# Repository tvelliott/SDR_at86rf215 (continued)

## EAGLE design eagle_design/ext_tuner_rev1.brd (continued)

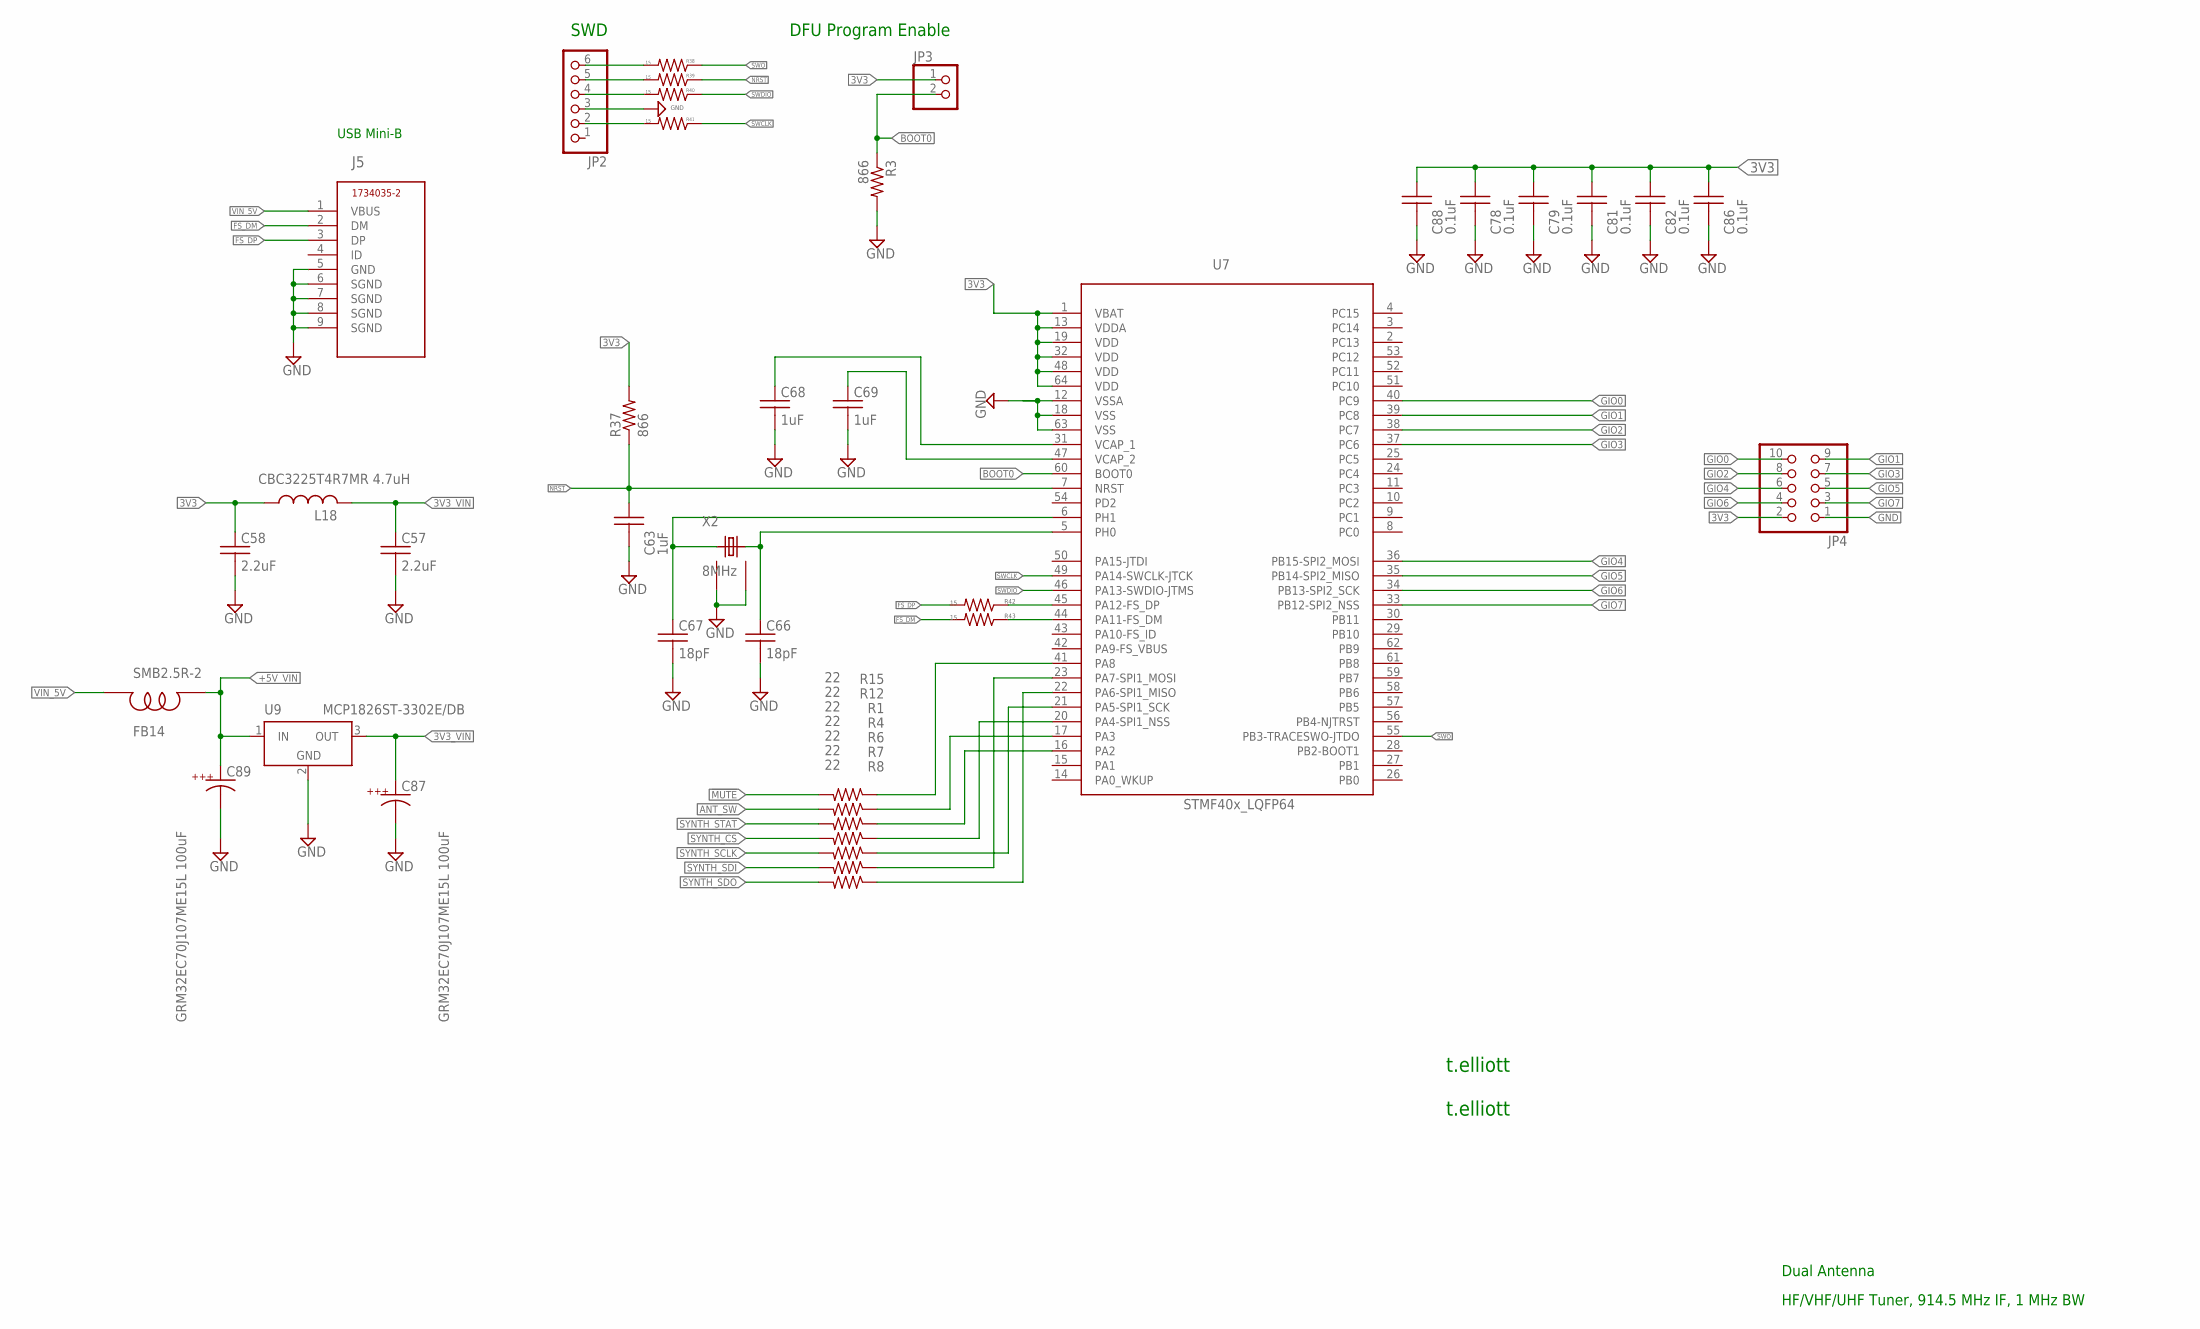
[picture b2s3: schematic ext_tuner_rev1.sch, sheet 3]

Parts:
C57, C58: 2.2uF; C0603
C63, C68, C69: 1uF; C0402@1
C66, C67: 18pF; C0402@1
C78, C79, C81, C82, C86, C88: 0.1uF; C0402@1
C87, C89: GRM32EC70J107ME15L 100uF; 1210K
FB14: SMB2.5R-2; SMB2.5-2
J5: 1734035-2
JP2: PINHD-1X6; 1X06
JP3: PINHD-1X2; 1X02
JP4: PINHD-2X5; 2X05
L18: CBC3225T4R7MR 4.7uH; L3225M; PARTNUMBER ELJ-PA331KF
R1, R4, R6, R7, R8, R12, R15: 22; R0603_COMPACT
R3: 866; R0603
R37: 866; 0603
R38, R39, R40, R41, R42, R43: 15; 0402$1
U7: STM32_STM32F40X_LQFP64RGT6; STM32_LQFP64
U9: MCP1826ST-3302E/DB; SOT223
X2: 8MHz; ECS_CRYSTAL_ECS-250-20-30B-DU_CRYSTAL

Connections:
3V3: C58.1, C78.1, C79.1, C81.1, C82.1, C86.1, C88.1, JP3.1, JP4.2, L18.1, R37.2, U7.1 (VBAT), U7.13 (VDDA), U7.19 (VDD), U7.32 (VDD), U7.48 (VDD), U7.64 (VDD); also elsewhere on the board
3V3_VIN: C57.1, C87.A, L18.2, U9.3 (OUT)
!MUTE: R15.2; also elsewhere on the board
+5V_VIN: C89.A, FB14.P$1, U9.1 (IN); also elsewhere on the board
ANT_SW: R12.2; also elsewhere on the board
BOOT0: JP3.2, R3.1, U7.60 (BOOT0)
FS_DM: J5.2 (DM), R43.2
FS_DP: J5.3 (DP), R42.2
GIO0: JP4.10, U7.40 (PC9)
GIO1: JP4.9, U7.39 (PC8)
GIO2: JP4.8, U7.38 (PC7)
GIO3: JP4.7, U7.37 (PC6)
GIO4: JP4.6, U7.36 (PB15-SPI2_MOSI)
GIO5: JP4.5, U7.35 (PB14-SPI2_MISO)
GIO6: JP4.4, U7.34 (PB13-SPI2_SCK)
GIO7: JP4.3, U7.33 (PB12-SPI2_NSS)
GND: C57.2, C58.2, C63.2, C66.2, C67.2, C68.2, C69.2, C78.2, C79.2, C81.2, C82.2, C86.2, C87.C, C88.2, C89.C, J5.5 (GND), J5.6 (SGND), J5.7 (SGND), J5.8 (SGND), J5.9 (SGND), JP2.3, JP4.1, R3.2, U7.12 (VSSA), U7.18 (VSS), U7.63 (VSS), U9.2 (GND), U9.4 (GND), X2.GND@1 (GND), X2.GND@2 (GND); also elsewhere on the board
unnamed: R6.1, U7.21 (PA5-SPI1_SCK)
unnamed: R8.1, U7.22 (PA6-SPI1_MISO)
unnamed: R7.1, U7.23 (PA7-SPI1_MOSI)
unnamed: R4.1, U7.20 (PA4-SPI1_NSS)
unnamed: C67.1, U7.6 (PH1), X2.1
unnamed: C66.1, U7.5 (PH0), X2.3
unnamed: R42.1, U7.45 (PA12-FS_DP)
unnamed: R43.1, U7.44 (PA11-FS_DM)
unnamed: C69.1, U7.47 (VCAP_2)
unnamed: C68.1, U7.31 (VCAP_1)
unnamed: JP2.6, R38.2
unnamed: JP2.5, R39.2
unnamed: JP2.4, R40.2
unnamed: JP2.2, R41.2
unnamed: R1.1, U7.16 (PA2)
unnamed: R12.1, U7.17 (PA3)
unnamed: R15.1, U7.41 (PA8)
NRST: C63.1, R37.1, R39.1, U7.7 (NRST)
SWCLK: R41.1, U7.49 (PA14-SWCLK-JTCK)
SWDIO: R40.1, U7.46 (PA13-SWDIO-JTMS)
SWO: R38.1, U7.55 (PB3-TRACESWO-JTDO)
SYNTH_CS: R4.2; also elsewhere on the board
SYNTH_SCLK: R6.2; also elsewhere on the board
SYNTH_SDI: R7.2; also elsewhere on the board
SYNTH_SDO: R8.2; also elsewhere on the board
SYNTH_STAT: R1.2; also elsewhere on the board
VIN_5V: FB14.P$2, J5.1 (VBUS)

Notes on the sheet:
SWD
USB Mini-B
t.elliott
Dual Antenna
DFU Program Enable
HF/VHF/UHF Tuner, 914.5 MHz IF, 1 MHz BW

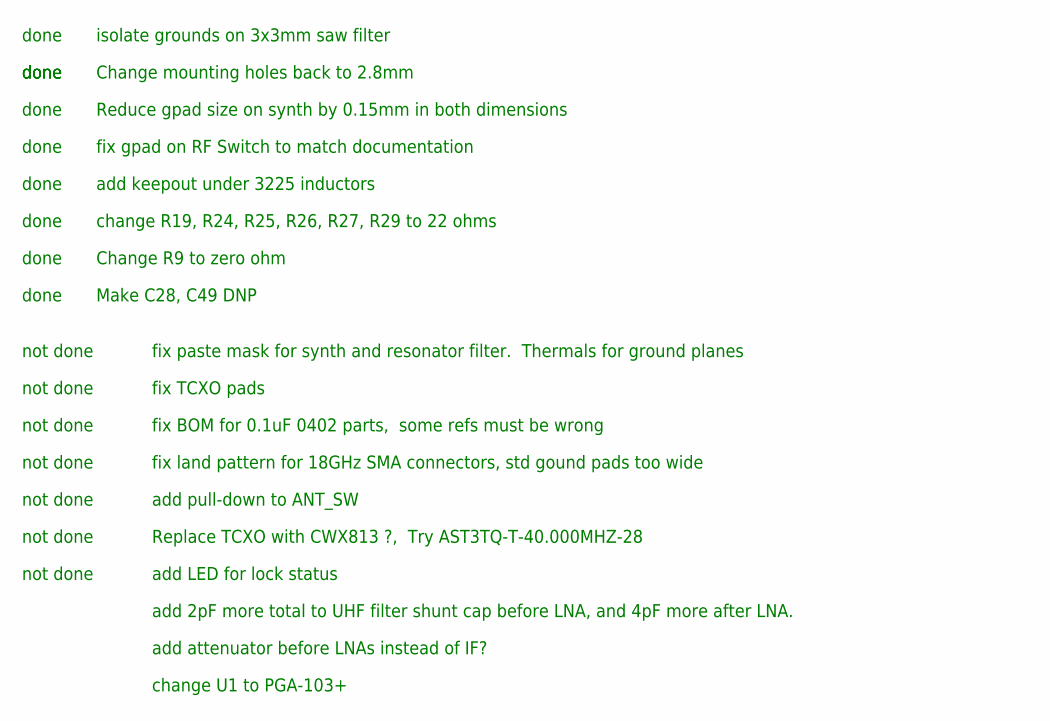
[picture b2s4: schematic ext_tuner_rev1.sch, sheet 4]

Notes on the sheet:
Change mounting holes back to 2.8mm
Reduce gpad size on synth by 0.15mm in both dimensions
fix gpad on RF Switch to match documentation
done
not done
fix paste mask for synth and resonator filter. Thermals for ground planes
fix TCXO pads
add keepout under 3225 inductors
fix BOM for 0.1uF 0402 parts, some refs must be wrong
fix land pattern for 18GHz SMA connectors, std gound pads too wide
add pull-down to ANT_SW
change R19, R24, R25, R26, R27, R29 to 22 ohms
Replace TCXO with CWX813 ?, Try AST3TQ-T-40.000MHZ-28
add LED for lock status
Change R9 to zero ohm
Make C28, C49 DNP
isolate grounds on 3x3mm saw filter
add 2pF more total to UHF filter shunt cap before LNA, and 4pF more after LNA.
add attenuator before LNAs instead of IF?
change U1 to PGA-103+

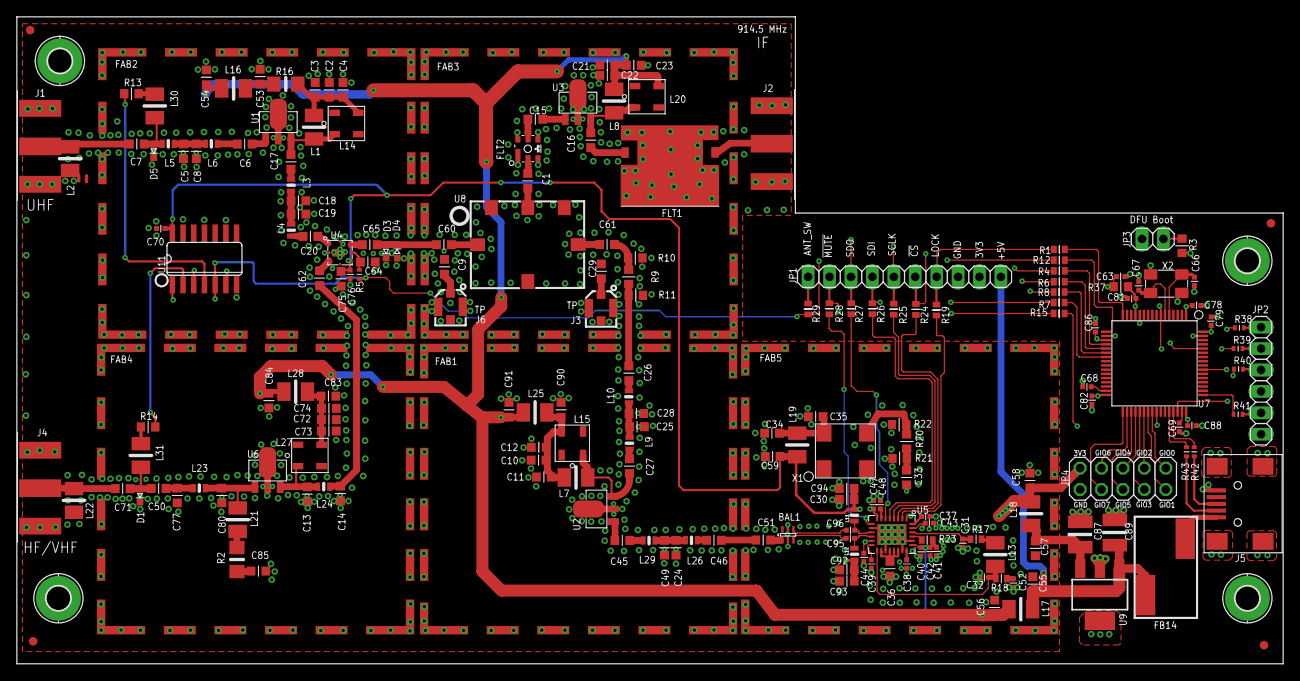
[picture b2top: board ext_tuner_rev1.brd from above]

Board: 4 copper layers, 150.2 x 76.7 mm, 206 parts (0 on the bottom side), 124 nets.

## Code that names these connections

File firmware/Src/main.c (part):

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        * Output
        * EVENT_OUT
        * EXTI
     PA8   ------> USB_OTG_FS_SOF
     PA11   ------> USB_OTG_FS_DM
     PA12   ------> USB_OTG_FS_DP
*/
static void MX_GPIO_Init( void )
{
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

  //display pins, all output
  //PG0 = DISP_RS
  //PG1 = DISP_SI
  //PG2 = DISP_CSB
  //PG3 = DISP_SCL
  //PG4 = DISP_RST
  GPIO_InitStruct.Pin = GPIO_PIN_0 | GPIO_PIN_1 | GPIO_PIN_2 | GPIO_PIN_3 | GPIO_PIN_4;
  GPIO_InitStruct.Mode = GPIO_MODE_OUTPUT_PP;
  GPIO_InitStruct.Pull = GPIO_NOPULL;
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

  //MCO2 output
  /*Configure GPIO pin : PC9 */
  GPIO_InitStruct.Pin = GPIO_PIN_9;
  GPIO_InitStruct.Mode = GPIO_MODE_AF_PP;
  GPIO_InitStruct.Pull = GPIO_NOPULL;
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
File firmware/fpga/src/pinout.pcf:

set_io AT_MISO B1
set_io AT_MOSI C1
set_io AT_SCLK D1
set_io AT_IRQ D2
set_io AT_CS C2
set_io AT_RESET_N R3
set_io FPGA_RXCLK J3
set_io FPGA_RX24 F1
set_io FPGA_TXCLK T3
set_io FPGA_TX_24_900 T2
set_io FPGA_RX900 T1
set_io LED2 A1 
set_io LED3 A2 
set_io clk_in R9 
set_io AUDIO_SDIN T8 
set_io AUDIO_SCLK T7 
set_io AUDIO_LRCLK T6 
set_io AUDIO_MCLK T5 
set_io CBSEL P13
set_io TUNER_SCK B10
set_io TUNER_MOSI B9
set_io TUNER_CS B8
set_io TUNER_MISO A9
set_io BT1 A5
set_io BT2 A6
set_io BT3 A7
set_io BT4 B5 
set_io BT5 B6 
set_io BT6 B7 
set_io A0 C16 
set_io A1 T15 
set_io A2 R16 
set_io A3 R15 
set_io A4 P16 
set_io A5 P15 
set_io A6 N16 
set_io A7 M16 
set_io A8 M15 
set_io A9 L16 
set_io A10 T14 
set_io A11 R14  
set_io A12 P14 
set_io A13 L14 
set_io A14 D14 
set_io A15 C14 
set_io D0 D16 
set_io D1 D15 
set_io D2 B16 
set_io D3 B15 
set_io D4 A16 
set_io D5 A15 
set_io D6 E16 
set_io D7 F15 
set_io D8 F16 
set_io D9 G15 
set_io D10 G16 
set_io D11 J15 
set_io D12 J16 
set_io D13 K15 
set_io D14 K16 
set_io D15 T16 
set_io FSMC_NOE F14 
set_io FSMC_NWE H14 
set_io FSMC_NE1 J14 
set_io FSMC_NE4 K14 
set_io FSMC_NL_NADV B14
set_io FPGA_SPI_SCLK R10
set_io FPGA_SPI_MOSI P10
set_io FPGA_SPI_MISO N12
set_io FPGA_SPI_CS R12 
set_io FSMC_CLK_IN K9 
set_io MIC_CLK R6 
set_io MIC_DATA R5 

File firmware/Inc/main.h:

//MIT License
//
//Copyright (c) 2018 tvelliott
//
//Permission is hereby granted, free of charge, to any person obtaining a copy
//of this software and associated documentation files (the "Software"), to deal
//in the Software without restriction, including without limitation the rights
//to use, copy, modify, merge, publish, distribute, sublicense, and/or sell
//copies of the Software, and to permit persons to whom the Software is
//furnished to do so, subject to the following conditions:
//
//The above copyright notice and this permission notice shall be included in all
//copies or substantial portions of the Software.
//
//THE SOFTWARE IS PROVIDED "AS IS", WITHOUT WARRANTY OF ANY KIND, EXPRESS OR
//IMPLIED, INCLUDING BUT NOT LIMITED TO THE WARRANTIES OF MERCHANTABILITY,
//FITNESS FOR A PARTICULAR PURPOSE AND NONINFRINGEMENT. IN NO EVENT SHALL THE
//AUTHORS OR COPYRIGHT HOLDERS BE LIABLE FOR ANY CLAIM, DAMAGES OR OTHER
//LIABILITY, WHETHER IN AN ACTION OF CONTRACT, TORT OR OTHERWISE, ARISING FROM,
//OUT OF OR IN CONNECTION WITH THE SOFTWARE OR THE USE OR OTHER DEALINGS IN THE
//SOFTWARE.



/* Define to prevent recursive inclusion -------------------------------------*/
#ifndef __MAIN_H__
#define __MAIN_H__

/* Includes ------------------------------------------------------------------*/

/* USER CODE BEGIN Includes */

/* USER CODE END Includes */

/* Private define ------------------------------------------------------------*/

#define MCO_Pin GPIO_PIN_9
#define MCO_GPIO_Port GPIOC
#define RMII_MDC_Pin GPIO_PIN_1
#define RMII_MDC_GPIO_Port GPIOC
#define RMII_REF_CLK_Pin GPIO_PIN_1
#define RMII_REF_CLK_GPIO_Port GPIOA
#define RMII_MDIO_Pin GPIO_PIN_2
#define RMII_MDIO_GPIO_Port GPIOA
#define RMII_CRS_DV_Pin GPIO_PIN_7
#define RMII_CRS_DV_GPIO_Port GPIOA
#define RMII_RXD0_Pin GPIO_PIN_4
#define RMII_RXD0_GPIO_Port GPIOC
#define RMII_RXD1_Pin GPIO_PIN_5
#define RMII_RXD1_GPIO_Port GPIOC
#define RMII_TXD1_Pin GPIO_PIN_14
#define RMII_TXD1_GPIO_Port GPIOG
#define LD3_Pin GPIO_PIN_3
#define LD3_GPIO_Port GPIOE
#define STLK_RX_Pin GPIO_PIN_11
#define STLK_RX_GPIO_Port GPIOB
#define STLK_TX_Pin GPIO_PIN_10
#define STLK_TX_GPIO_Port GPIOB
#define TMS_Pin GPIO_PIN_13
#define TMS_GPIO_Port GPIOA
#define TCK_Pin GPIO_PIN_14
#define TCK_GPIO_Port GPIOA
#define RMII_TX_EN_Pin GPIO_PIN_11
#define RMII_TX_EN_GPIO_Port GPIOG
#define RMII_TXD0_Pin GPIO_PIN_13
#define RMII_TXD0_GPIO_Port GPIOG
#define SWO_Pin GPIO_PIN_3
#define SWO_GPIO_Port GPIOB
#define LD2_Pin GPIO_PIN_2
#define LD2_GPIO_Port GPIOE

/* ########################## Assert Selection ############################## */
/**
  * @brief Uncomment the line below to expanse the "assert_param" macro in the
  *        HAL drivers code
  */
/* #define USE_FULL_ASSERT    1U */

/* USER CODE BEGIN Private defines */

/* USER CODE END Private defines */

#ifdef __cplusplus
extern "C" {
#endif
void _Error_Handler( char *, int );

#define Error_Handler() _Error_Handler(__FILE__, __LINE__)
#ifdef __cplusplus
}
#endif

#endif /* __MAIN_H__ */

/************************ (C) COPYRIGHT STMicroelectronics *****END OF FILE****/

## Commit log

2022-07-24 add design files
2022-07-24 add fpga routing images
2022-07-24 add firmware and HDL / verilog
2022-07-24 add eagle design files for the external tuner
2022-07-24 add firmware for external tuner
2022-07-24 add ext tuner design
2022-07-25 rename pdf dir
2022-07-25 update eagle files and schematic to reflect changes made to receiver when ext tuner was added
2022-07-26 remove unused
